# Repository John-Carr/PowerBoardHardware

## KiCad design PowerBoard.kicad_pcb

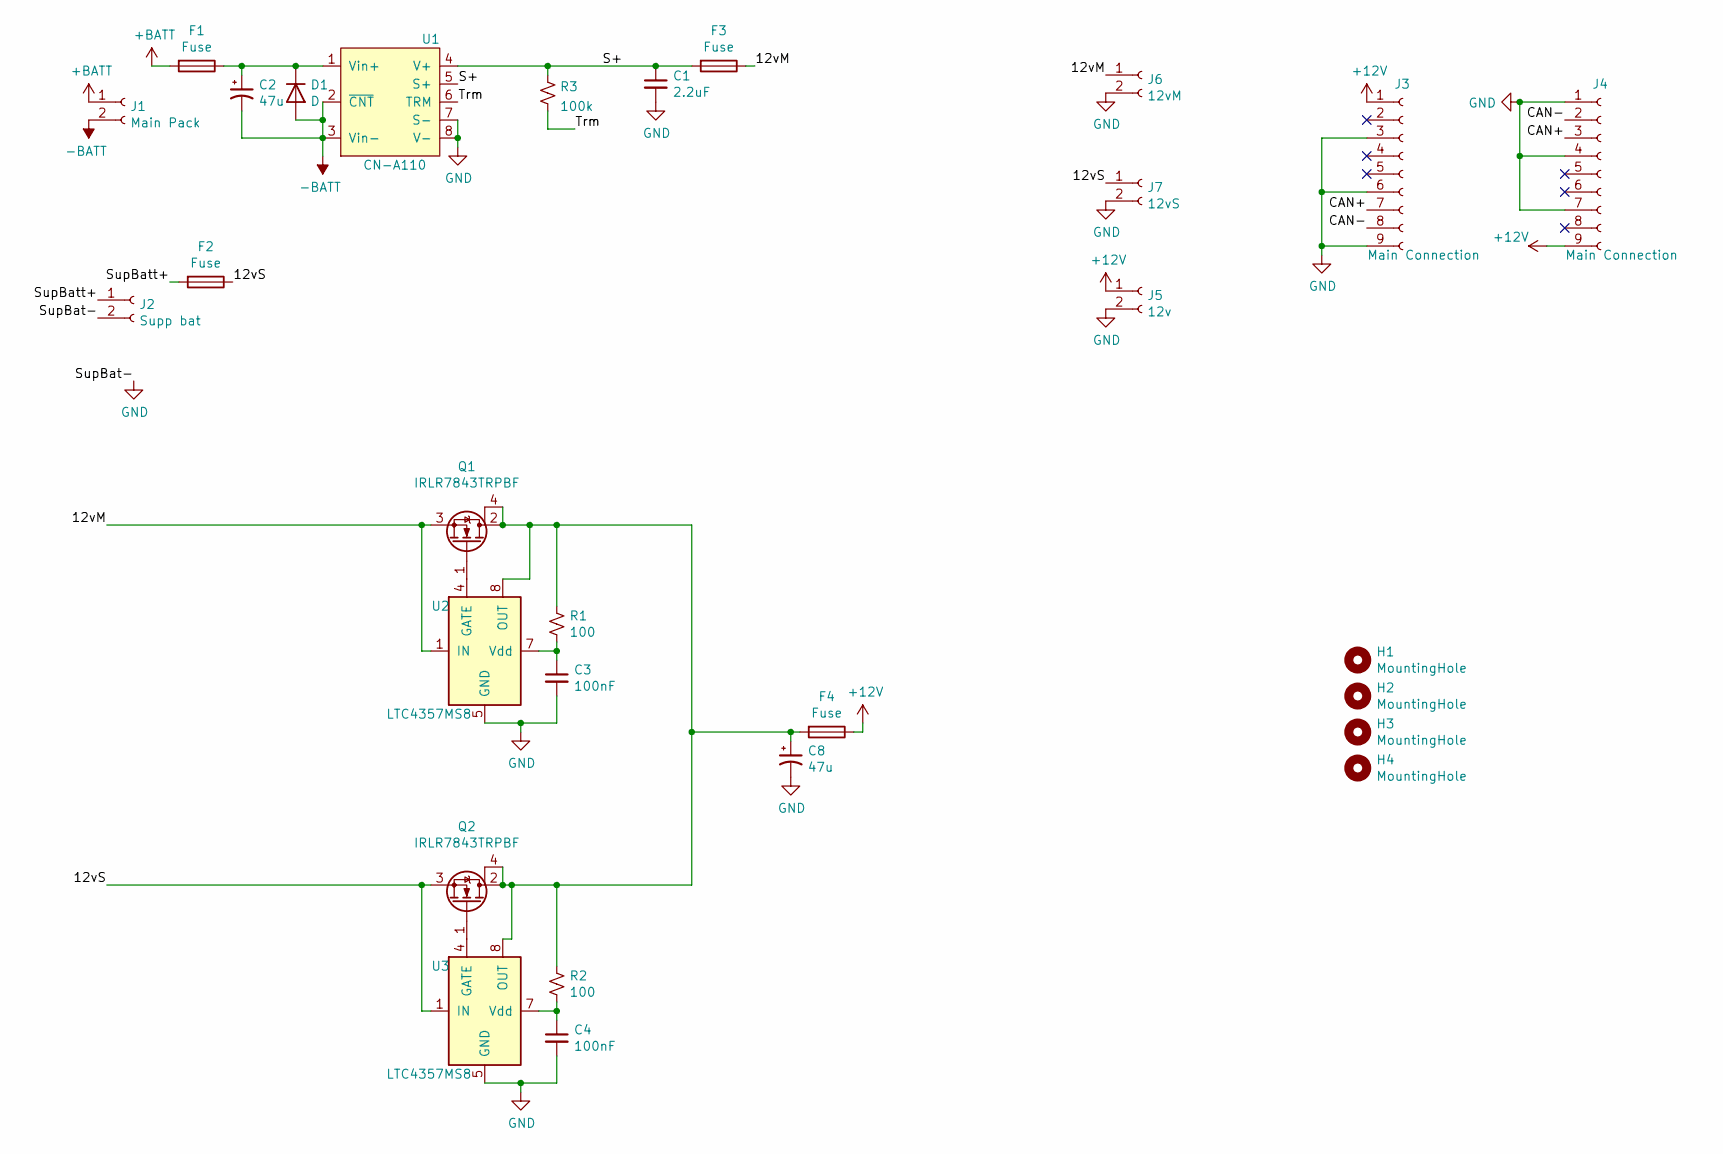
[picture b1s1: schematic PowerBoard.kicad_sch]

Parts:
C1: 2.2uF; C_0805_2012Metric; LCSC# C28323
C2: 47u; CP_Radial_D12.5mm_P5.00mm
C3, C4: 100nF; C_0603_1608Metric; LCSC# C14663
C8: 47u; CP_Elec_10x10
D1: D; D_SOD-123F; LCSC# C64898
F1, F2, F3, F4: Fuse; KeystoneFuseHolder3557-2
H1, H2, H3, H4: MountingHole; MountingHole_3.2mm_M3
J1: Main Pack; Molex_Micro-Fit_3.0_43650-0215_1x02_P3.00mm_Vertical
J2: Supp bat; Molex_Micro-Fit_3.0_43650-0215_1x02_P3.00mm_Vertical
J3, J4: Main Connection; Molex_Micro-Fit_3.0_43650-0915_1x09_P3.00mm_Vertical
J5: 12v; Molex_Micro-Fit_3.0_43650-0215_1x02_P3.00mm_Vertical
J6: 12vM; Molex_Micro-Fit_3.0_43650-0215_1x02_P3.00mm_Vertical
J7: 12vS; Molex_Micro-Fit_3.0_43650-0215_1x02_P3.00mm_Vertical
Q1, Q2: IRLR7843TRPBF; TO-252-3_TabPin4; LCSC# C21988
R1, R2: 100; R_0603_1608Metric; LCSC# C22775
R3: 100k; R_1206_3216Metric_Pad1.30x1.75mm_HandSolder
U1: CN-A110; CN100a110
U2, U3: LTC4357MS8; MSOP-8_3x3mm_P0.65mm

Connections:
+12V: F4.1, J3.1, J4.9, J5.1
+BATT: F1.2, J1.1
-BATT: C2.2, D1.2 (A), J1.2, U1.2 (~CNT), U1.3 (Vin-)
/12vM: F3.1, J6.1, Q1.3 (S), U2.1 (IN)
/12vS: F2.1, J7.1, Q2.3 (S), U3.1 (IN)
/CAN+: J3.7, J4.3
/CAN-: J3.8, J4.2
/S+: C1.1, F3.2, R3.1, U1.4 (V+), U1.5 (S+)
/SupBatt+: F2.2, J2.1
/Trm: R3.2, U1.6 (TRM)
GND: C1.2, C3.2, C4.2, C8.2, J2.2, J3.3, J3.6, J3.9, J4.1, J4.4, J4.7, J5.2, J6.2, J7.2, U1.7 (S-), U1.8 (V-), U2.5 (GND), U3.5 (GND)
unnamed: C2.1, D1.1 (K), F1.1, U1.1 (Vin+)
unnamed: C3.1, R1.2, U2.7 (Vdd)
unnamed: C4.1, R2.2, U3.7 (Vdd)
unnamed: C8.1, F4.2, Q1.2 (D), Q1.4 (D), Q2.2 (D), Q2.4 (D), R1.1, R2.1, U2.8 (OUT), U3.8 (OUT)
unnamed: Q1.1 (G), U2.4 (GATE)
unnamed: Q2.1 (G), U3.4 (GATE)

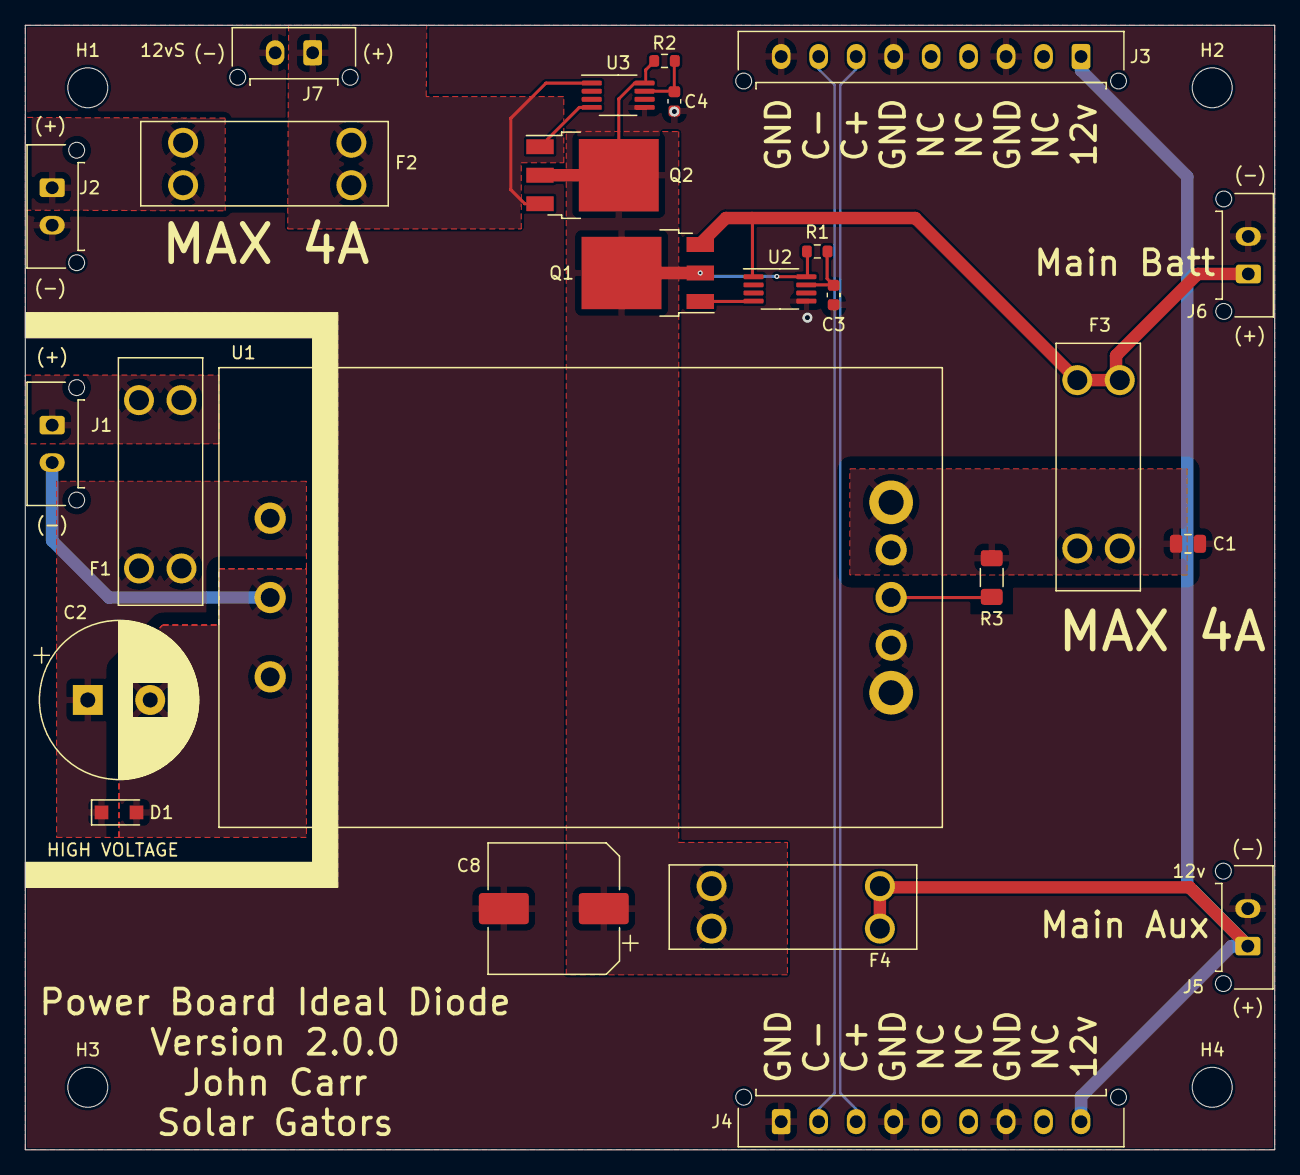
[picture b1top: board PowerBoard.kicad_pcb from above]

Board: 2 copper layers, 100.0 x 90.0 mm, 29 parts (0 on the bottom side), 17 nets.

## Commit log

2022-02-24 Initial work
2022-06-16 Adding automation
2022-06-16 Remove backups
2022-06-16 Revision 2 (#1)
    * Initial work
    * Adding automation
2022-06-16 Fix for automation
